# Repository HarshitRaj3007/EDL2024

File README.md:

# EDL2024
Repository for our EDL project in year 2024. RRAM Characterization using FPGA.

This repository contains the PCB design files of all the three modules (Main PCB, Resisitive crossbar array, Power PCB), HDL code, Python code used for GUI, and PCB enclosure design files.

There are 3 files for documentation:
1. Documentation for programming, laptop-FPGA interface & GUI
2. Documentation for PCB
3. Documentation for Testing(mainly Analog)

**HDL files**: EDL_merged_code encapsulates all the HDL code and the .py files for GUI. folder has a readme file that holds detailed information about the directory.

**PCB files**: MiniCircuit contains KiCAD files for a scaled-down version of the PCB intended for testing, FinalCircuit contains design files of the main PCB module, ResistiveCrossbar contains design files for a 3 $\times$ 3 resistive crossbar array and PowerConverter has the design files for the power PCB which was intended to power the entire module from wall supply of 230 V AC. 

**CAD files**: A basic PCB enclosure which can be fabricated via laser cutting can be found in the Enclosure_Fusion360.dxf file. Couldn't add the .stp file for the reference 3D design of the complete circuit due to file size restrictions in GitHub. 

**Operating Procedure**

Since the power PCB module we designed turned out to be faulty, we had to use power banks instead to supply $\pm$ 5 V, which have to connected appropriately to the corresponding pins in the main PCB module. The final design is highly user-friendly and all one needs to do after this step is to provide the parameters under which the characterization is to be executed: amplitude of the input pulse, the location of the resistor in the array, the mode of operation (RD/WR) and the requisite $R_{sense}$ location. The GUI displays both the input and output waveform for a pulse width of 100 $\mu s$, along with the estimated value of the resistance.

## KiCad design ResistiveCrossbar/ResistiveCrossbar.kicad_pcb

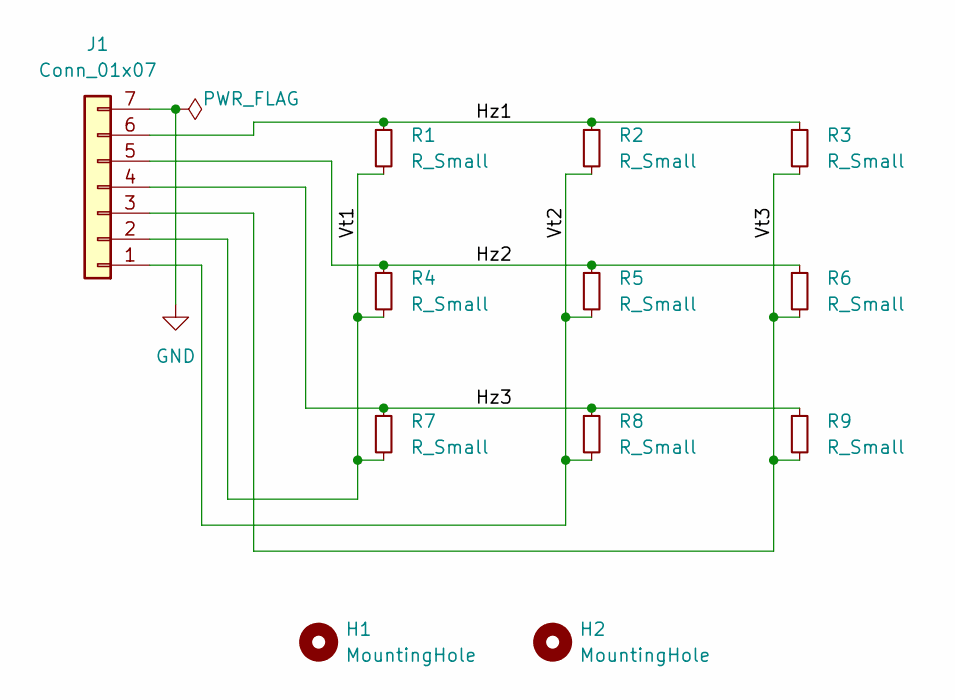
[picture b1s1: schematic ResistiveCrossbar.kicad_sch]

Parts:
H1, H2: MountingHole; MountingHole_3mm
J1: Conn_01x07; PinHeader_1x07_P2.54mm_Vertical
R1, R2, R3, R4, R5, R6, R7, R8, R9: R_Small; R_1206_3216Metric_Pad1.30x1.75mm_HandSolder

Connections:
/Hz1: J1.6, R1.1, R2.1, R3.1
/Hz2: J1.5, R4.1, R5.1, R6.1
/Hz3: J1.4, R7.1, R8.1, R9.1
/Vt1: J1.2, R1.2, R4.2, R7.2
/Vt2: J1.1, R2.2, R5.2, R8.2
/Vt3: J1.3, R3.2, R6.2, R9.2
GND: J1.7

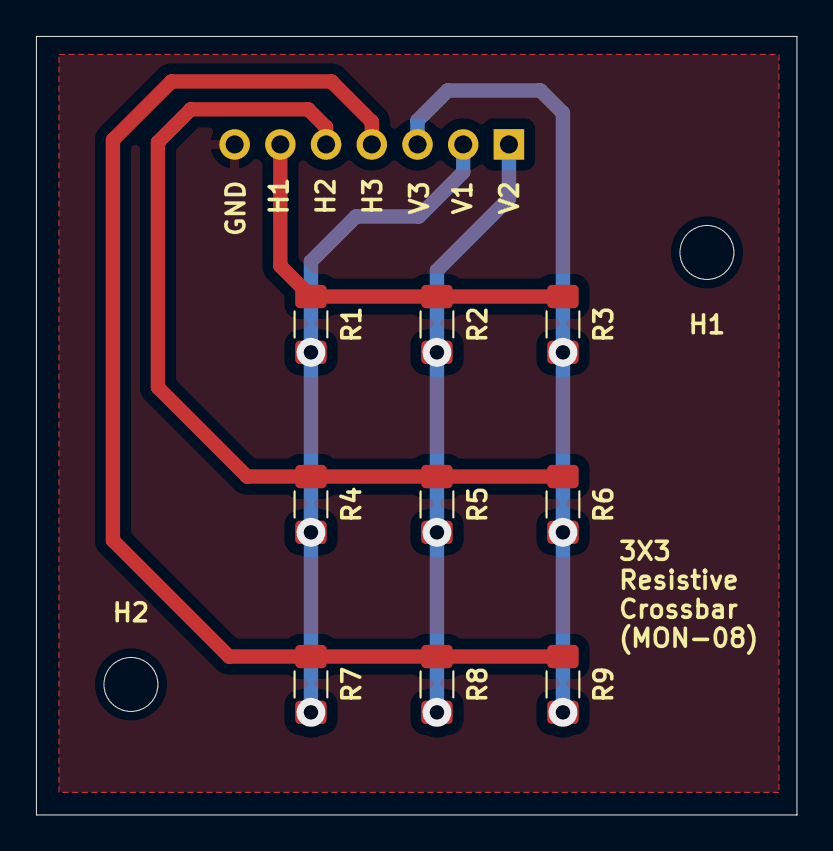
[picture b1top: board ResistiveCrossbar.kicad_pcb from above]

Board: 2 copper layers, 42.2 x 43.2 mm, 12 parts (1 on the bottom side), 6 nets.

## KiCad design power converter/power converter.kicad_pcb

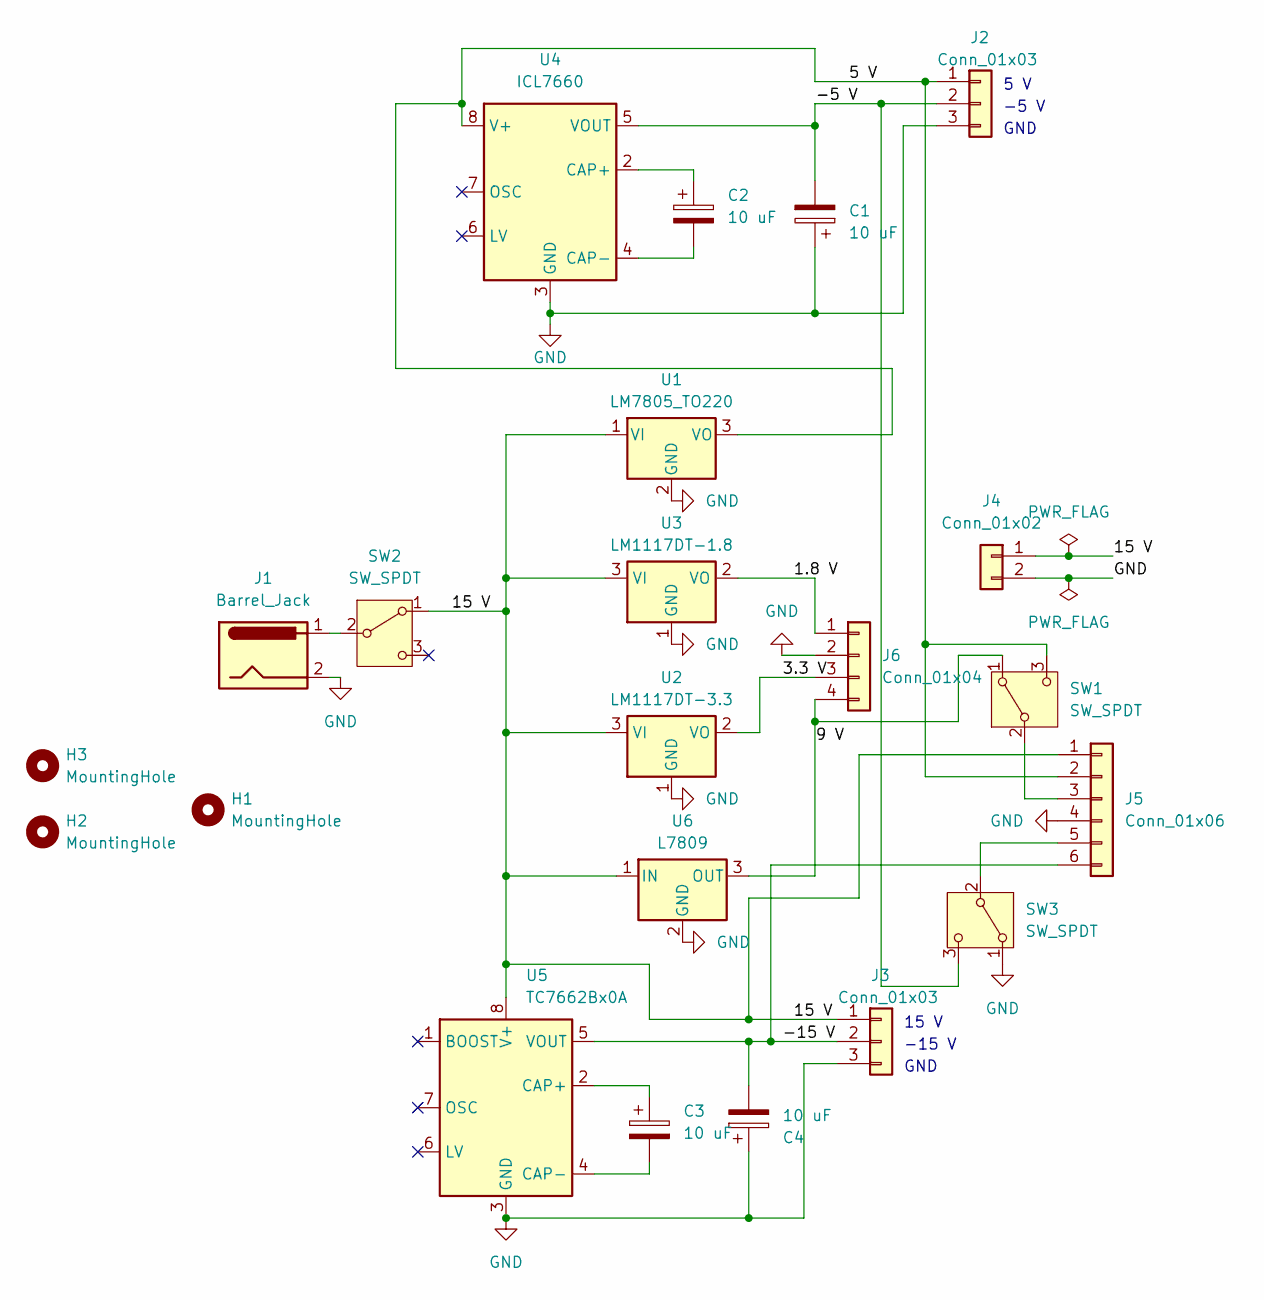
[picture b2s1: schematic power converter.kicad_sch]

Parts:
C1, C2, C3, C4: 10 uF; CP_Radial_D5.0mm_P2.50mm
H1, H2, H3: MountingHole; MountingHole_3mm
J1: Barrel_Jack; BarrelJack_Horizontal
J2, J3: Conn_01x03; PinHeader_1x03_P2.54mm_Vertical
J4: Conn_01x02; PinHeader_1x02_P2.54mm_Vertical
J5: Conn_01x06; PinSocket_1x06_P2.54mm_Vertical
J6: Conn_01x04; PinSocket_1x04_P2.54mm_Vertical
SW1, SW2, SW3: SW_SPDT; Slide_switch
U1: LM7805_TO220; TO-220-3_Vertical
U2: LM1117DT-3.3; TO-252-3_TabPin2
U3: LM1117DT-1.8; TO-252-3_TabPin2
U4: ICL7660; SOIC-8_3.9x4.9mm_P1.27mm
U5: TC7662Bx0A; SOIC-8_3.9x4.9mm_P1.27mm
U6: L7809; TO-220-3_Vertical

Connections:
/1.8 V: J6.1, U3.2 (VO)
/3.3 V: J6.3, U2.2 (VO)
/5 V: J2.1, J5.2, SW1.3 (C), U1.3 (VO), U4.8 (V+)
/9 V: J6.4, SW1.1 (A), U6.3 (OUT)
/15 V: J3.1, J4.1, J5.1, SW2.1 (A), U1.1 (VI), U2.3 (VI), U3.3 (VI), U5.8 (V+), U6.1 (IN)
/-5 V: C1.2, J2.2, SW3.3 (C), U4.5 (VOUT)
/-15 V: C4.2, J3.2, J5.6, U5.5 (VOUT)
GND: C1.1, C4.1, J1.2, J2.3, J3.3, J4.2, J5.4, J6.2, SW3.1 (A), U1.2 (GND), U2.1 (GND), U3.1 (GND), U4.3 (GND), U5.3 (GND), U6.2 (GND)
unnamed: J5.3, SW1.2 (B)
unnamed: J5.5, SW3.2 (B)
unnamed: J1.1, SW2.2 (B)
unnamed: C2.1, U4.2 (CAP+)
unnamed: C2.2, U4.4 (CAP-)
unnamed: C3.1, U5.2 (CAP+)
unnamed: C3.2, U5.4 (CAP-)

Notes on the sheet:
5 V
-15 V
GND
-5 V
15 V

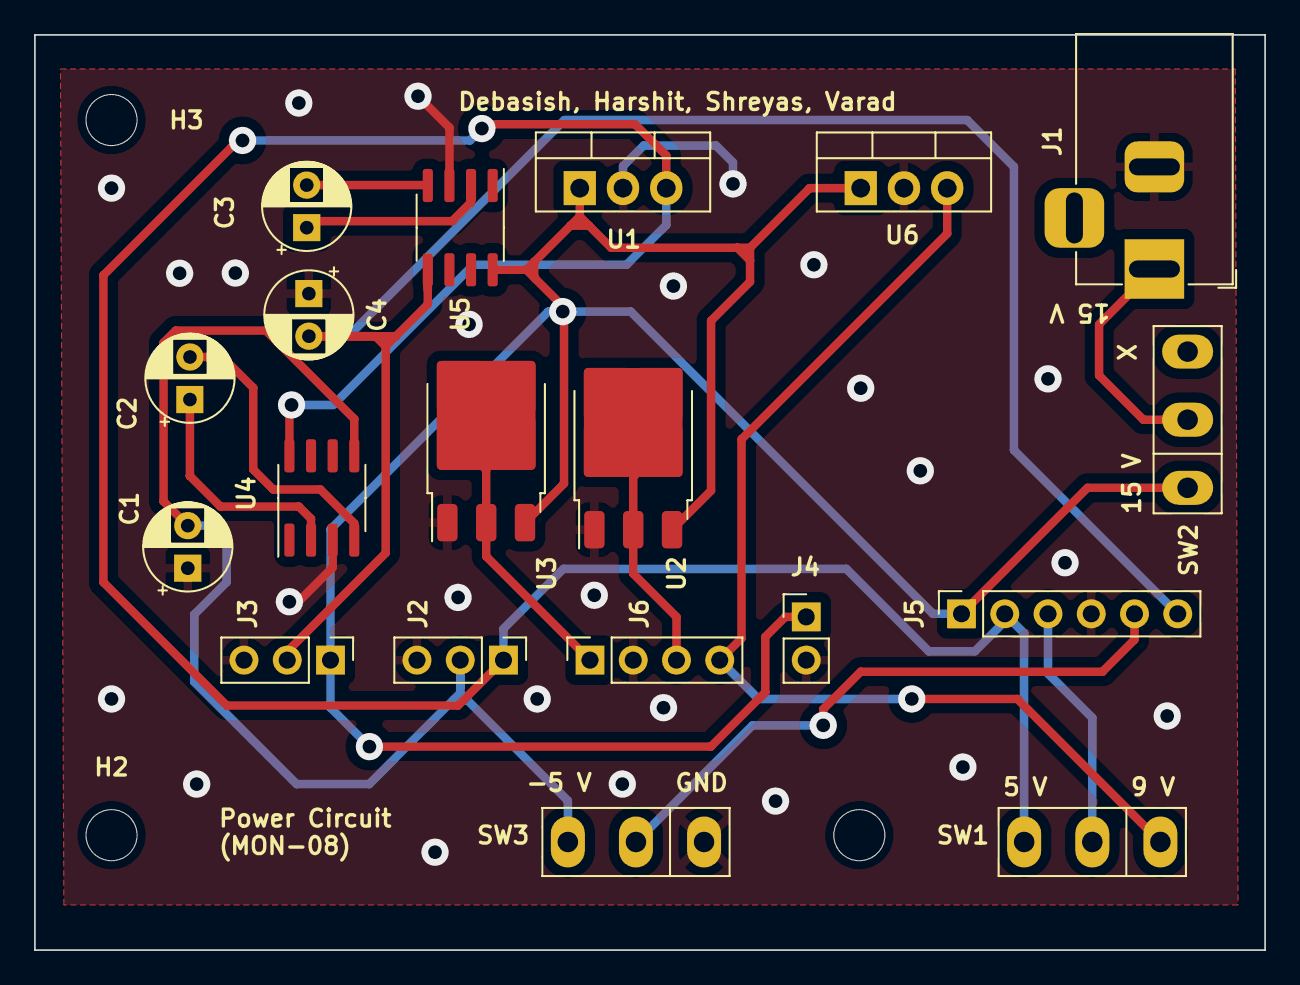
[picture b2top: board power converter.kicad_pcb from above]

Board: 2 copper layers, 72.2 x 53.8 mm, 22 parts (0 on the bottom side), 15 nets.

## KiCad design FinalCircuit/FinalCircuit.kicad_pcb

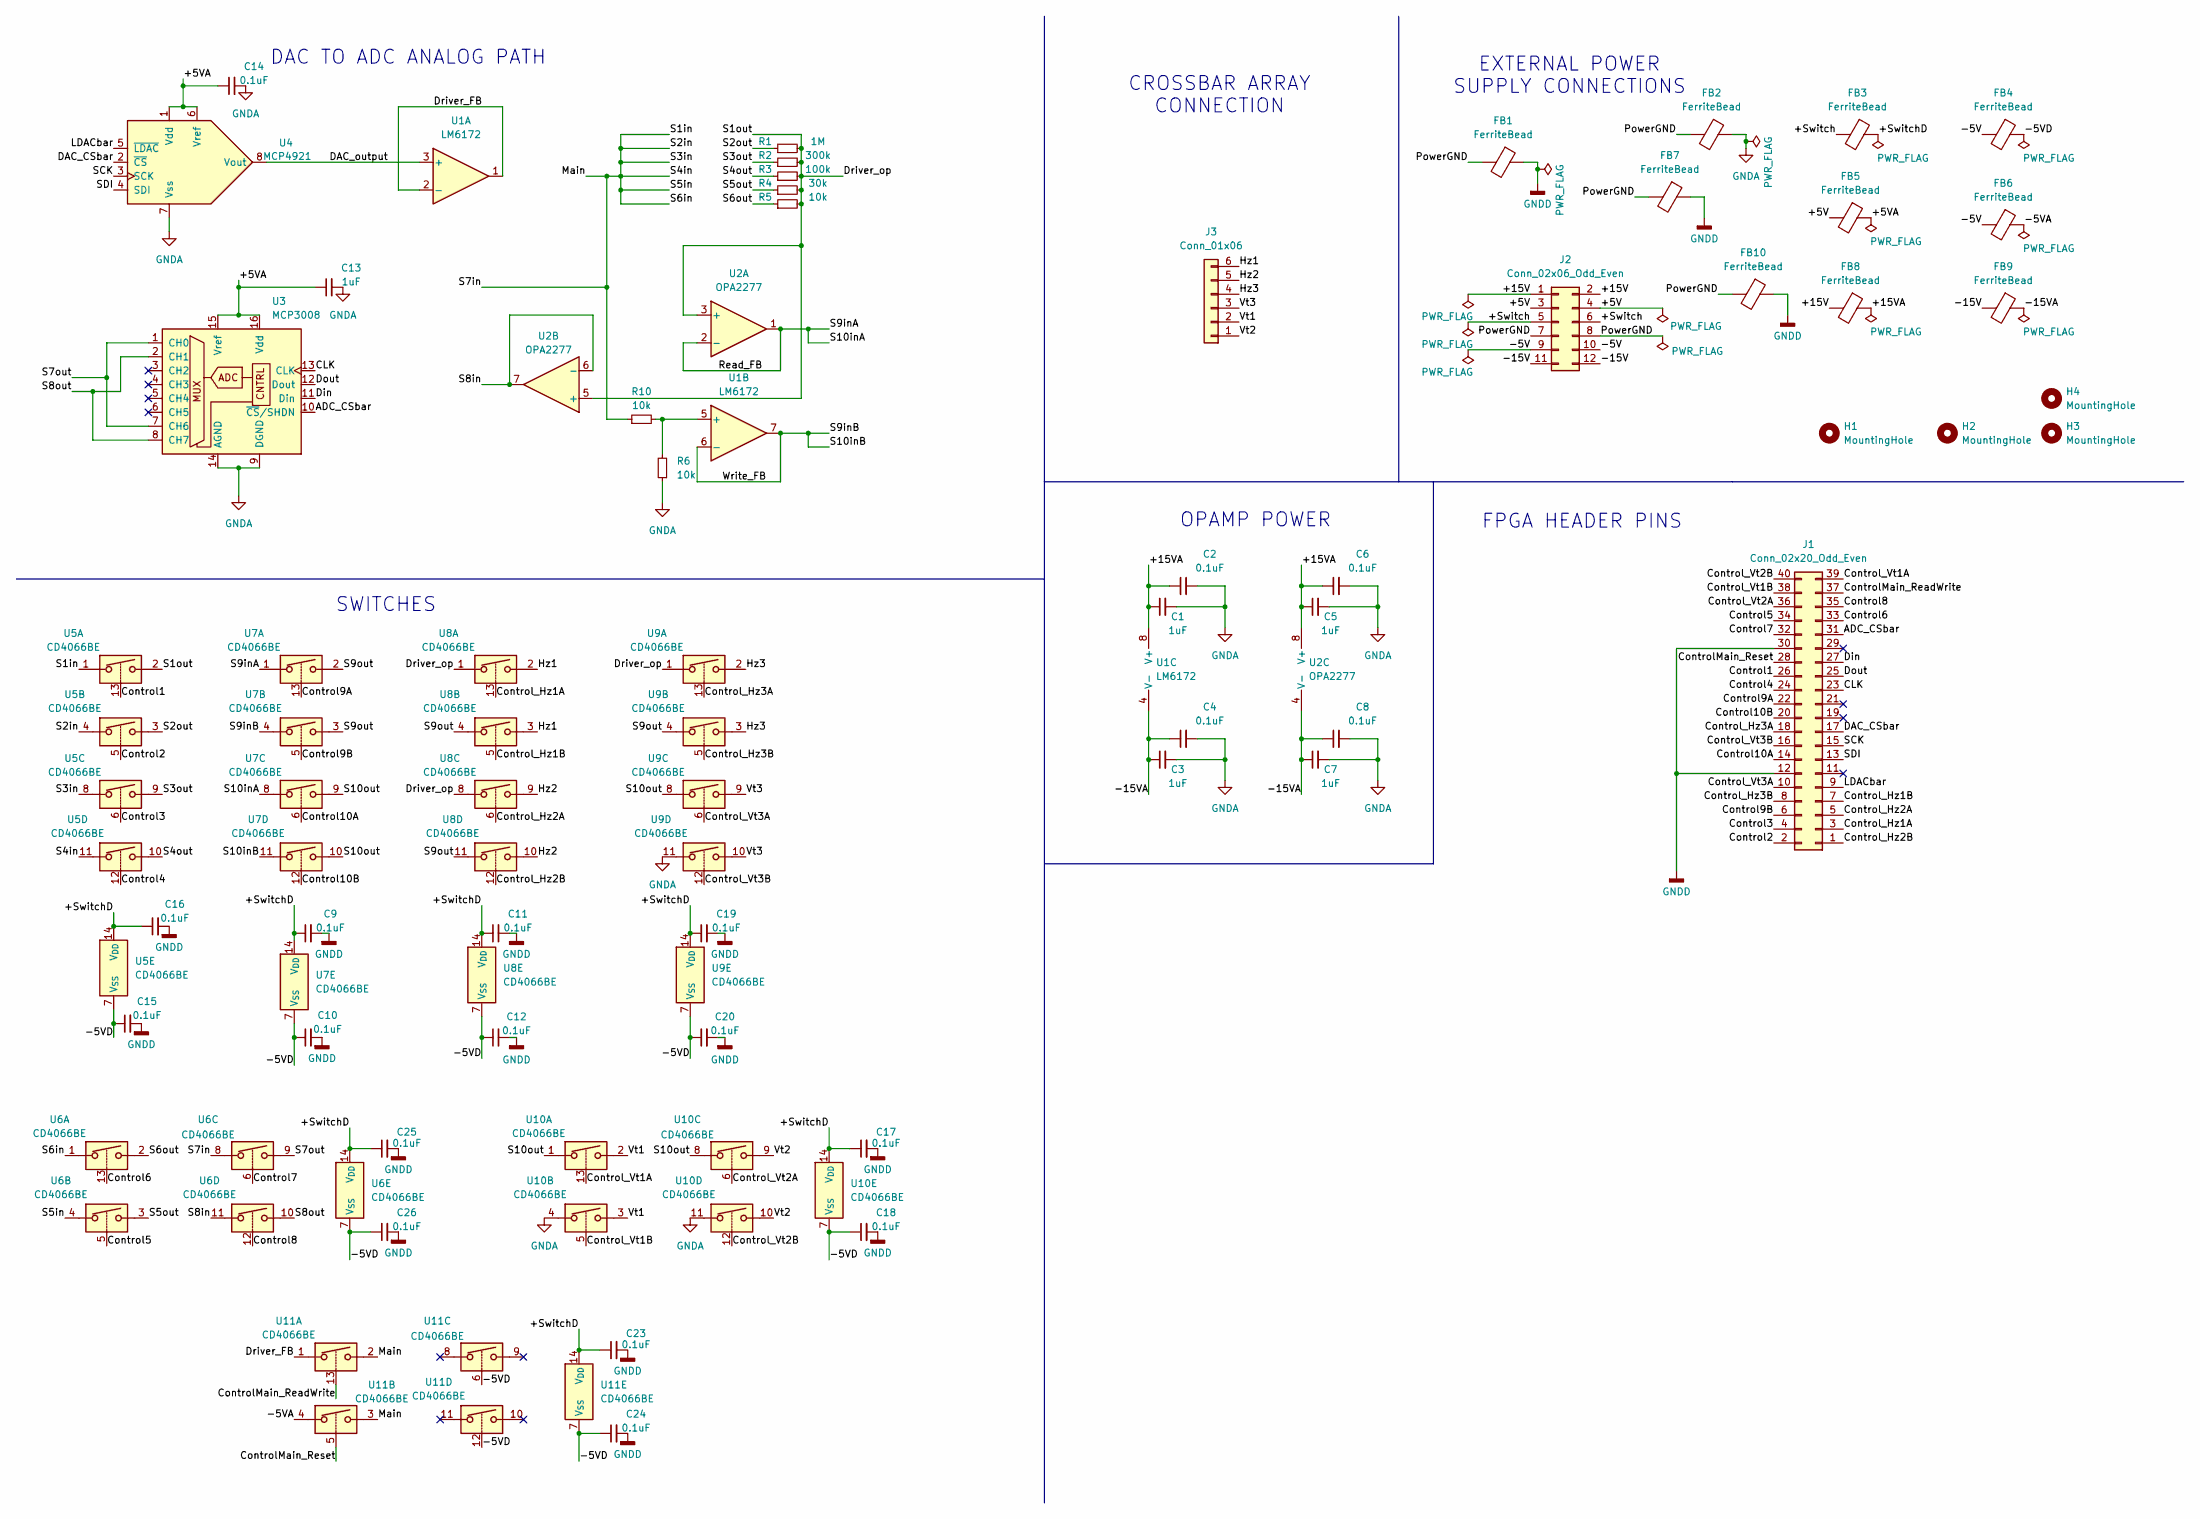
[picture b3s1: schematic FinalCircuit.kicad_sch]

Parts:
C1, C3, C5, C7, C13: 1uF; C_1206_3216Metric_Pad1.33x1.80mm_HandSolder
C2, C4, C6, C8, C9, C10, C11, C12, C14, C15, C16, C17, C18, C19, C20, C23, C24, C25, C26: 0.1uF; C_1206_3216Metric_Pad1.33x1.80mm_HandSolder
FB1, FB2, FB3, FB4, FB5, FB6, FB7, FB8, FB9, FB10: FerriteBead; L_0805_2012Metric_Pad1.15x1.40mm_HandSolder
H1, H2, H3, H4: MountingHole; MountingHole_3mm
J1: Conn_02x20_Odd_Even; PinSocket_2x20_P2.54mm_Vertical
J2: Conn_02x06_Odd_Even; PinHeader_2x06_P2.54mm_Vertical
J3: Conn_01x06; PinSocket_1x06_P2.54mm_Vertical
R1: 1M; R_1206_3216Metric_Pad1.30x1.75mm_HandSolder
R2: 300k; R_1206_3216Metric_Pad1.30x1.75mm_HandSolder
R3: 100k; R_1206_3216Metric_Pad1.30x1.75mm_HandSolder
R4: 30k; R_1206_3216Metric_Pad1.30x1.75mm_HandSolder
R5, R6, R10: 10k; R_1206_3216Metric_Pad1.30x1.75mm_HandSolder
U1: LM6172; DIP-8_W7.62mm_Socket
U2: OPA2277; DIP-8_W7.62mm_Socket
U3: MCP3008; DIP-16_W7.62mm_Socket
U4: MCP4921; DIP-8_W7.62mm_Socket
U5, U6, U7, U8, U9, U10, U11: CD4066BE; DIP-14_W7.62mm_Socket

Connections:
/+5V: FB5.2, J2.3, J2.4
/+5VA: C13.1, C14.1, FB5.1, U3.15 (Vref), U3.16 (Vdd), U4.1 (Vdd), U4.6 (Vref)
/+15V: FB8.2, J2.1, J2.2
/+15VA: C1.1, C2.1, C5.1, C6.1, FB8.1, U1.8 (V+), U2.8 (V+)
/+Switch: FB3.2, J2.5, J2.6
/+SwitchD: C9.1, C11.1, C16.1, C17.1, C19.1, C23.1, C25.1, FB3.1, U5.14 (V_{DD}), U6.14 (V_{DD}), U7.14 (V_{DD}), U8.14 (V_{DD}), U9.14 (V_{DD}), U10.14 (V_{DD}), U11.14 (V_{DD})
/-5V: FB4.2, FB6.2, J2.9, J2.10
/-5VA: FB6.1, U11.4
/-5VD: C10.1, C12.1, C15.1, C18.1, C20.1, C24.1, C26.1, FB4.1, U5.7 (V_{SS}), U6.7 (V_{SS}), U7.7 (V_{SS}), U8.7 (V_{SS}), U9.7 (V_{SS}), U10.7 (V_{SS}), U11.6, U11.7 (V_{SS}), U11.12
/-15V: FB9.2, J2.11, J2.12
/-15VA: C3.1, C4.1, C7.1, C8.1, FB9.1, U1.4 (V-), U2.4 (V-)
/ADC_CSbar: J1.31, U3.10 (~CS/SHDN)
/CLK: J1.23, U3.13 (CLK)
/Control1: J1.26, U5.13
/Control2: J1.2, U5.5
/Control3: J1.4, U5.6
/Control4: J1.24, U5.12
/Control5: J1.34, U6.5
/Control6: J1.33, U6.13
/Control7: J1.32, U6.6
/Control8: J1.35, U6.12
/Control9A: J1.22, U7.13
/Control9B: J1.6, U7.5
/Control10A: J1.14, U7.6
/Control10B: J1.20, U7.12
/ControlMain_ReadWrite: J1.37, U11.13
/ControlMain_Reset: J1.28, U11.5
/Control_Hz1A: J1.3, U8.13
/Control_Hz1B: J1.7, U8.5
/Control_Hz2A: J1.5, U8.6
/Control_Hz2B: J1.1, U8.12
/Control_Hz3A: J1.18, U9.13
/Control_Hz3B: J1.8, U9.5
/Control_Vt1A: J1.39, U10.13
/Control_Vt1B: J1.38, U10.5
/Control_Vt2A: J1.36, U10.6
/Control_Vt2B: J1.40, U10.12
/Control_Vt3A: J1.10, U9.6
/Control_Vt3B: J1.16, U9.12
/DAC_CSbar: J1.17, U4.2 (~CS)
/DAC_output: U1.3 (+), U4.8 (Vout)
/Din: J1.27, U3.11 (Din)
/Dout: J1.25, U3.12 (Dout)
/Driver_FB: U1.1, U1.2 (-), U11.1
/Driver_op: R1.2, R2.2, R3.2, R4.2, R5.2, U2.3 (+), U2.5 (+), U5.2, U8.1, U8.8, U9.1
/Hz1: J3.6, U8.2, U8.3
/Hz2: J3.5, U8.9, U8.10
/Hz3: J3.4, U9.2, U9.3
/LDACbar: J1.9, U4.5 (~LDAC)
/Main: R10.1, U5.1, U5.4, U5.8, U5.11, U6.1, U6.4, U6.8, U11.2, U11.3
/PowerGND: FB1.2, FB2.2, FB7.2, FB10.2, J2.7, J2.8
/Read_FB: U2.1, U2.2 (-), U7.1, U7.8
/S2out: R1.1, U5.3
/S3out: R2.1, U5.9
/S4out: R3.1, U5.10
/S5out: R4.1, U6.3
/S6out: R5.1, U6.2
/S7out: U3.1 (CH0), U3.7 (CH6), U6.9
/S8in: U2.6 (-), U2.7, U6.11
/S8out: U3.2 (CH1), U3.8 (CH7), U6.10
/S9out: U7.2, U7.3, U8.4, U8.11, U9.4
/S10inB: U1.6 (-), U1.7, U7.4, U7.11
/S10out: U7.9, U7.10, U9.8, U10.1, U10.8
/SCK: J1.15, U4.3 (SCK)
/SDI: J1.13, U4.4 (SDI)
/Vt1: J3.2, U10.2, U10.3
/Vt2: J3.1, U10.9, U10.10
/Vt3: J3.3, U9.9, U9.10
GNDA: C1.2, C2.2, C3.2, C4.2, C5.2, C6.2, C7.2, C8.2, C13.2, C14.2, FB2.1, R6.1, U3.9 (DGND), U3.14 (AGND), U4.7 (Vss), U9.11, U10.4, U10.11
GNDD: C9.2, C10.2, C11.2, C12.2, C15.2, C16.2, C17.2, C18.2, C19.2, C20.2, C23.2, C24.2, C25.2, C26.2, FB1.1, FB7.1, FB10.1, J1.12, J1.30
unnamed: R6.2, R10.2, U1.5 (+)

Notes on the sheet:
SWITCHES
CROSSBAR ARRAY CONNECTION
DAC TO ADC ANALOG PATH
OPAMP POWER
EXTERNAL POWER SUPPLY CONNECTIONS
FPGA HEADER PINS

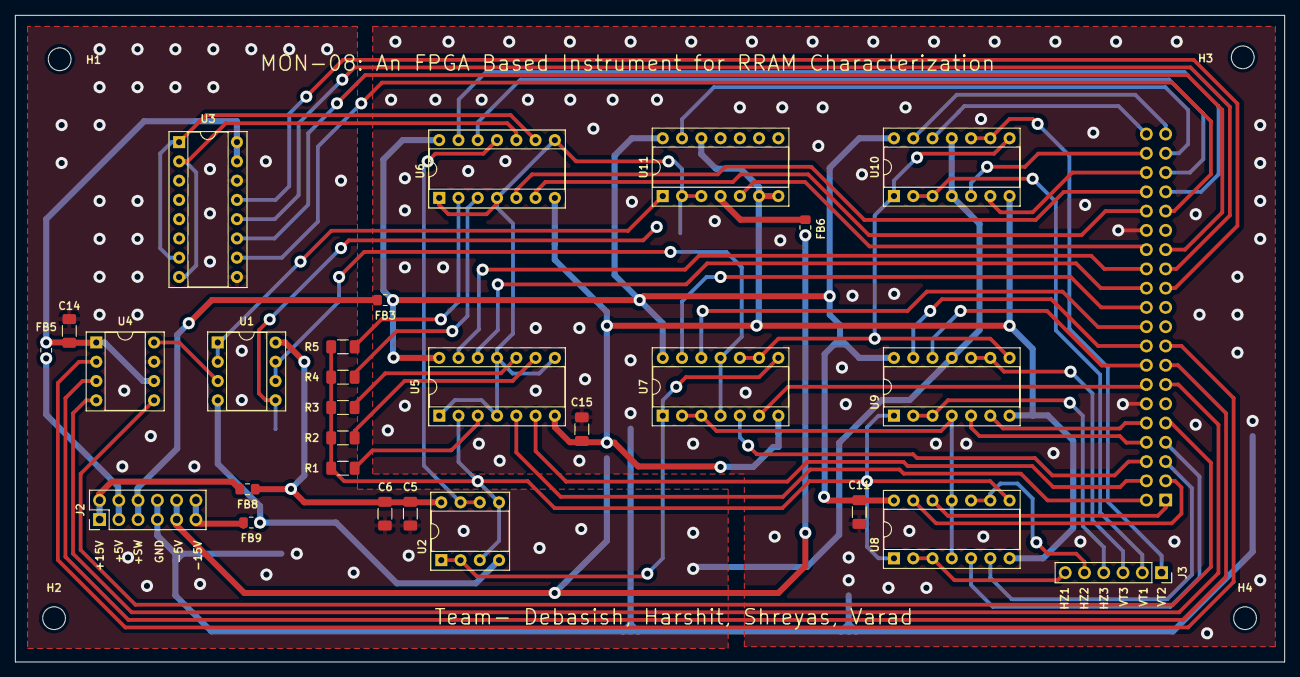
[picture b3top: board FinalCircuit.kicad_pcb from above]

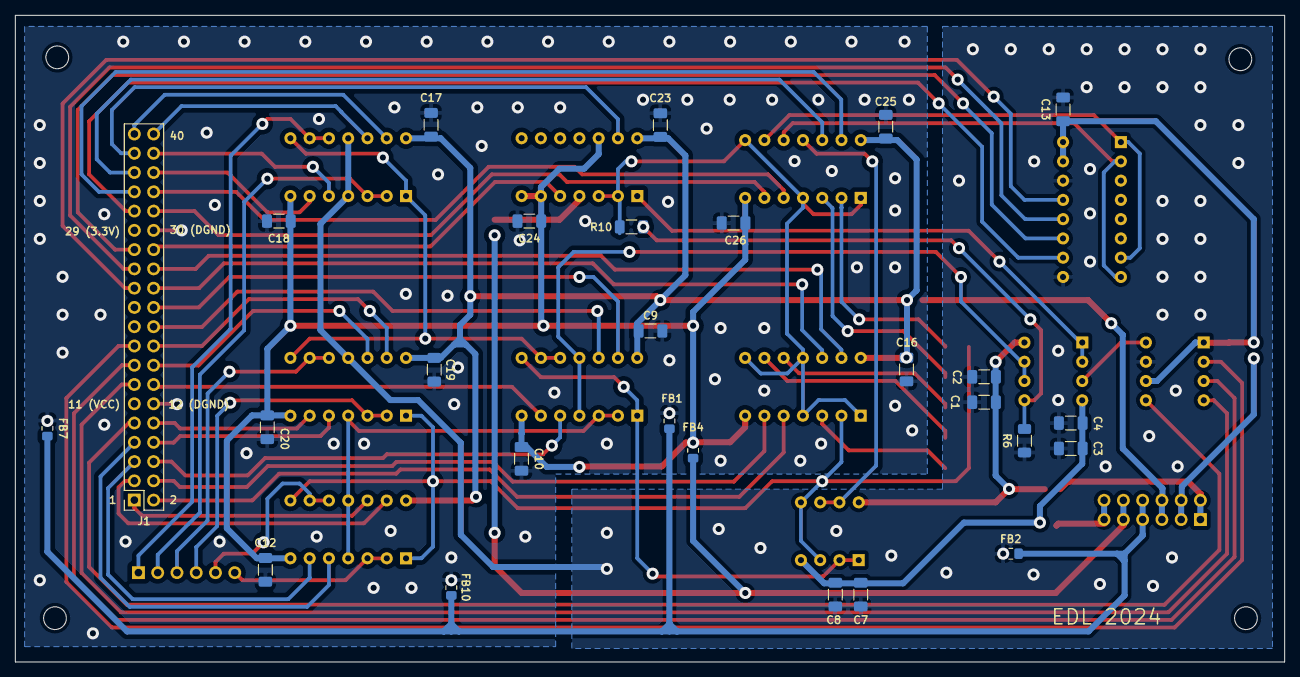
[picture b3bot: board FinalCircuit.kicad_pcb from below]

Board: 2 copper layers, 167.3 x 85.2 mm, 59 parts (27 on the bottom side), 71 nets.

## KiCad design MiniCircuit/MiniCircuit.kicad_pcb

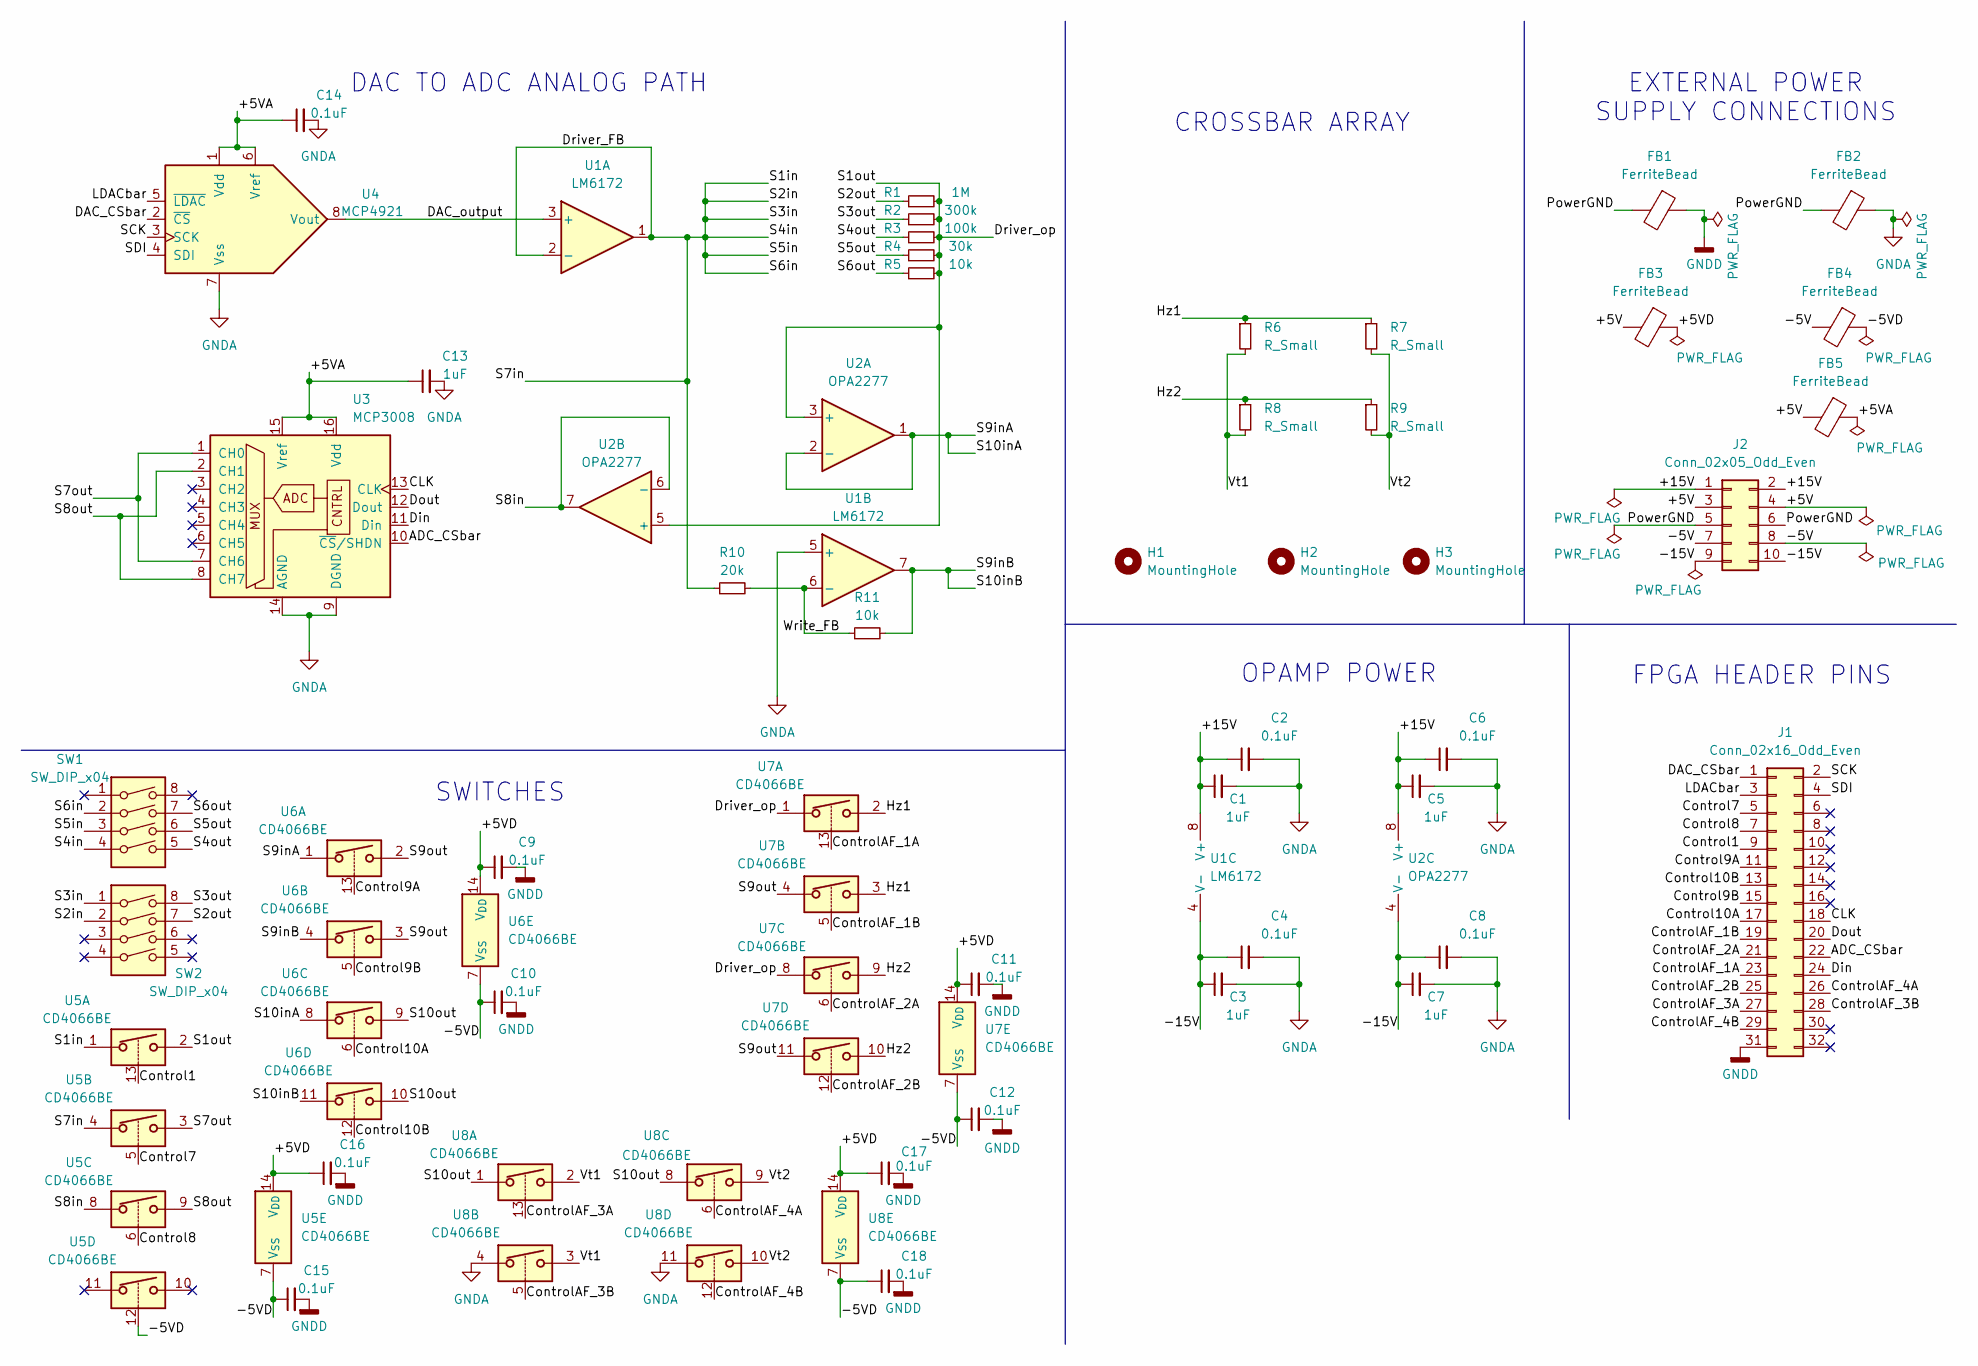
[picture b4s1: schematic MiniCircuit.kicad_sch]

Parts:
C1, C3, C5, C7, C13: 1uF; C_1206_3216Metric_Pad1.33x1.80mm_HandSolder
C2, C4, C6, C8, C9, C10, C11, C12, C14, C15, C16, C17, C18: 0.1uF; C_1206_3216Metric_Pad1.33x1.80mm_HandSolder
FB1, FB2, FB3, FB4, FB5: FerriteBead; L_0805_2012Metric_Pad1.15x1.40mm_HandSolder
H1, H2, H3: MountingHole; MountingHole_3mm
J1: Conn_02x16_Odd_Even; PinSocket_2x16_P2.54mm_Vertical
J2: Conn_02x05_Odd_Even; PinHeader_2x05_P2.54mm_Vertical
R1: 1M; R_1206_3216Metric_Pad1.30x1.75mm_HandSolder
R2: 300k; R_1206_3216Metric_Pad1.30x1.75mm_HandSolder
R3: 100k; R_1206_3216Metric_Pad1.30x1.75mm_HandSolder
R4: 30k; R_1206_3216Metric_Pad1.30x1.75mm_HandSolder
R5, R11: 10k; R_1206_3216Metric_Pad1.30x1.75mm_HandSolder
R6, R7, R8, R9: R_Small; R_1206_3216Metric_Pad1.30x1.75mm_HandSolder
R10: 20k; R_1206_3216Metric_Pad1.30x1.75mm_HandSolder
SW1, SW2: SW_DIP_x04; SW_DIP_SPSTx04_Slide_9.78x12.34mm_W7.62mm_P2.54mm
U1: LM6172; DIP-8_W7.62mm_Socket
U2: OPA2277; DIP-8_W7.62mm_Socket
U3: MCP3008; DIP-16_W7.62mm_Socket
U4: MCP4921; DIP-8_W7.62mm_Socket
U5, U6, U7, U8: CD4066BE; DIP-14_W7.62mm_Socket

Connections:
/+5V: FB3.2, FB5.2, J2.3, J2.4
/+5VA: C13.1, C14.1, FB5.1, U3.15 (Vref), U3.16 (Vdd), U4.1 (Vdd), U4.6 (Vref)
/+5VD: C9.1, C11.1, C16.1, C17.1, FB3.1, U5.14 (V_{DD}), U6.14 (V_{DD}), U7.14 (V_{DD}), U8.14 (V_{DD})
/+15V: C1.1, C2.1, C5.1, C6.1, J2.1, J2.2, U1.8 (V+), U2.8 (V+)
/-5V: FB4.2, J2.7, J2.8
/-5VD: C10.1, C12.1, C15.1, C18.1, FB4.1, U5.7 (V_{SS}), U5.12, U6.7 (V_{SS}), U7.7 (V_{SS}), U8.7 (V_{SS})
/-15V: C3.1, C4.1, C7.1, C8.1, J2.9, J2.10, U1.4 (V-), U2.4 (V-)
/ADC_CSbar: J1.22, U3.10 (~CS/SHDN)
/CLK: J1.18, U3.13 (CLK)
/Control1: J1.9, U5.13
/Control7: J1.5, U5.5
/Control8: J1.7, U5.6
/Control9A: J1.11, U6.13
/Control9B: J1.15, U6.5
/Control10A: J1.17, U6.6
/Control10B: J1.13, U6.12
/ControlAF_1A: J1.23, U7.13
/ControlAF_1B: J1.19, U7.5
/ControlAF_2A: J1.21, U7.6
/ControlAF_2B: J1.25, U7.12
/ControlAF_3A: J1.27, U8.13
/ControlAF_3B: J1.28, U8.5
/ControlAF_4A: J1.26, U8.6
/ControlAF_4B: J1.29, U8.12
/DAC_CSbar: J1.1, U4.2 (~CS)
/DAC_output: U1.3 (+), U4.8 (Vout)
/Din: J1.24, U3.11 (Din)
/Dout: J1.20, U3.12 (Dout)
/Driver_FB: R10.1, SW1.2, SW1.3, SW1.4, SW2.1, SW2.2, U1.1, U1.2 (-), U5.1, U5.4
/Driver_op: R1.2, R2.2, R3.2, R4.2, R5.2, U2.3 (+), U2.5 (+), U5.2, U7.1, U7.8
/Hz1: R6.1, R7.1, U7.2, U7.3
/Hz2: R8.1, R9.1, U7.9, U7.10
/LDACbar: J1.3, U4.5 (~LDAC)
/PowerGND: FB1.2, FB2.2, J2.5, J2.6
/S2out: R1.1, SW2.7
/S3out: R2.1, SW2.8
/S4out: R3.1, SW1.5
/S5out: R4.1, SW1.6
/S6out: R5.1, SW1.7
/S7out: U3.1 (CH0), U3.7 (CH6), U5.3
/S8in: U2.6 (-), U2.7, U5.8
/S8out: U3.2 (CH1), U3.8 (CH7), U5.9
/S9out: U6.2, U6.3, U7.4, U7.11
/S10inA: U2.1, U2.2 (-), U6.1, U6.8
/S10inB: R11.2, U1.7, U6.4, U6.11
/S10out: U6.9, U6.10, U8.1, U8.8
/SCK: J1.2, U4.3 (SCK)
/SDI: J1.4, U4.4 (SDI)
/Vt1: R6.2, R8.2, U8.2, U8.3
/Vt2: R7.2, R9.2, U8.9, U8.10
/Write_FB: R10.2, R11.1, U1.6 (-)
GNDA: C1.2, C2.2, C3.2, C4.2, C5.2, C6.2, C7.2, C8.2, C13.2, C14.2, FB2.1, U1.5 (+), U3.9 (DGND), U3.14 (AGND), U4.7 (Vss), U8.4, U8.11
GNDD: C9.2, C10.2, C11.2, C12.2, C15.2, C16.2, C17.2, C18.2, FB1.1, J1.31

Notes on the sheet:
SWITCHES
CROSSBAR ARRAY
DAC TO ADC ANALOG PATH
OPAMP POWER
EXTERNAL POWER SUPPLY CONNECTIONS
FPGA HEADER PINS

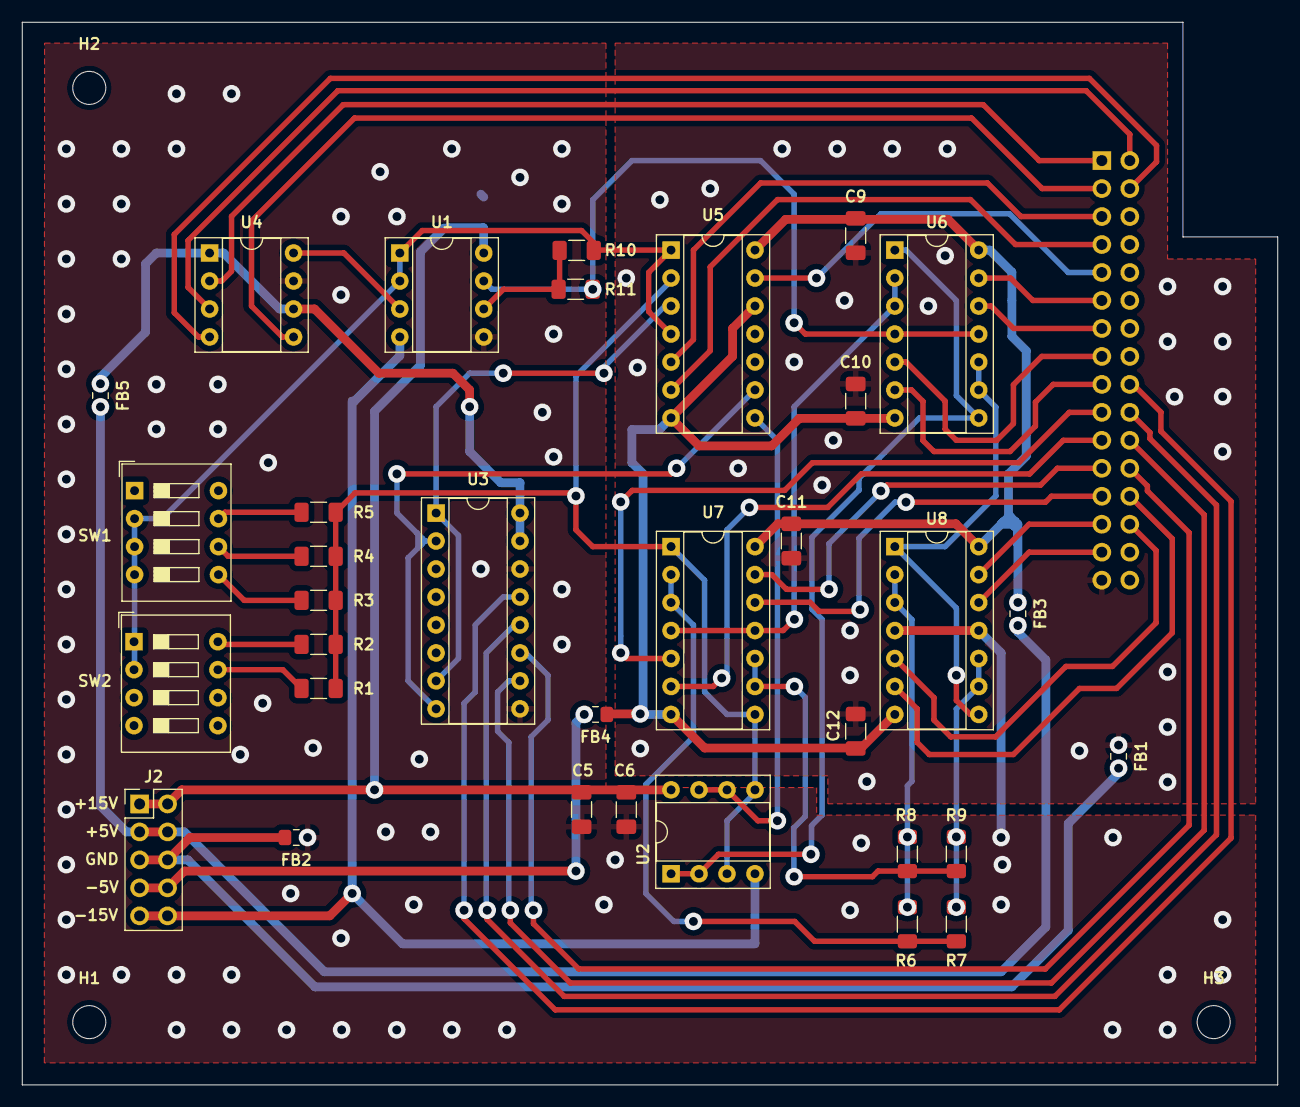
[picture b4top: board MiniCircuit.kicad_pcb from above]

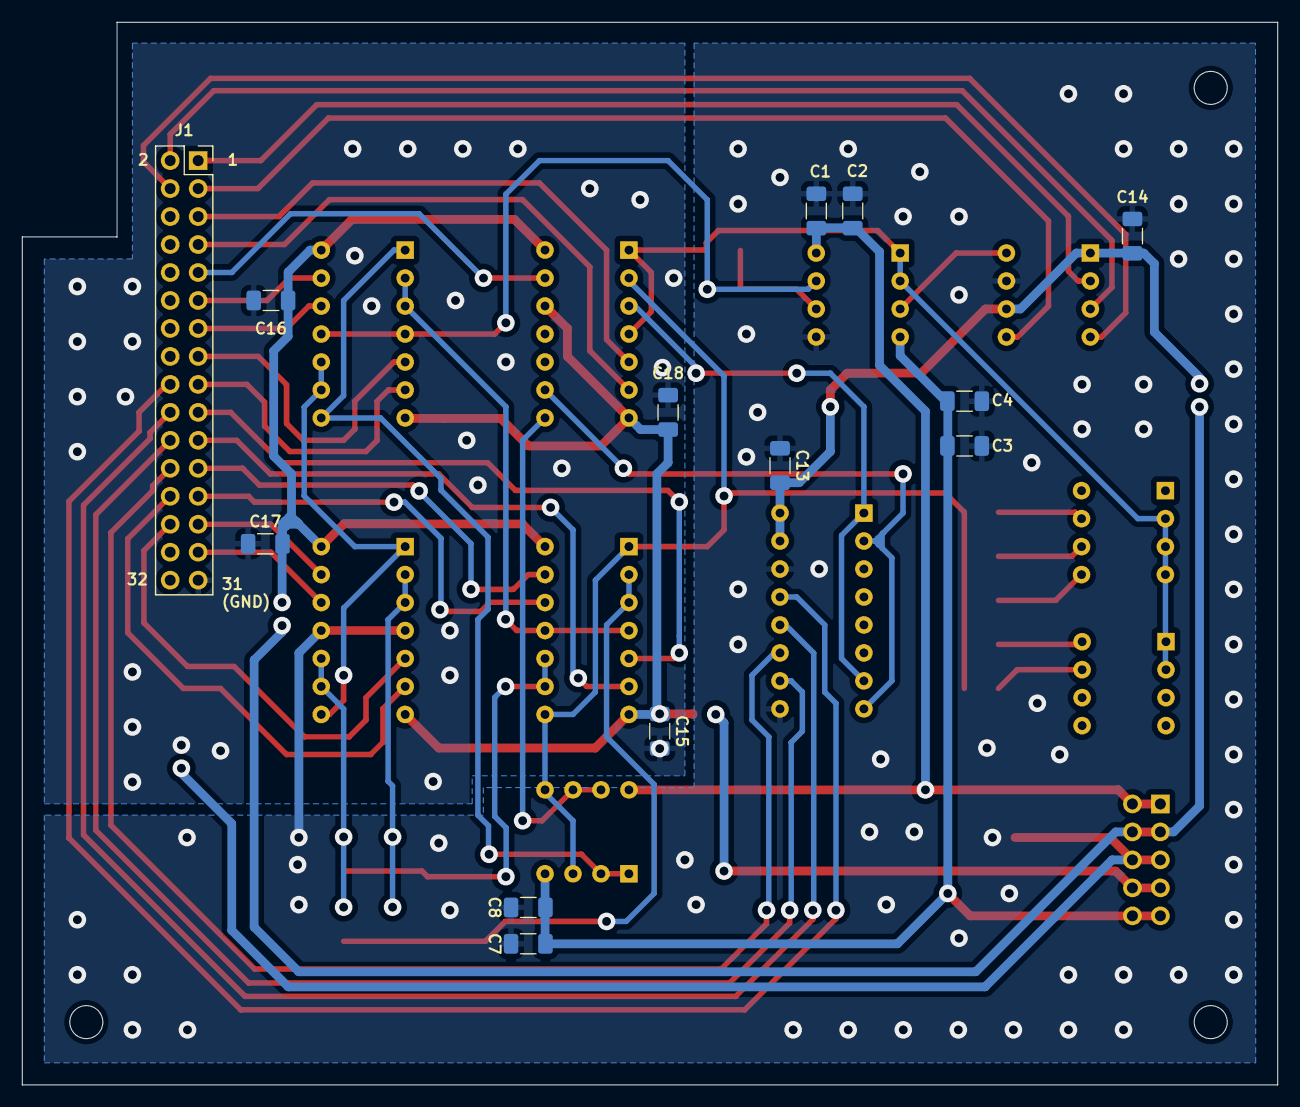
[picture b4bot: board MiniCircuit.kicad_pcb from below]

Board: 2 copper layers, 114.0 x 96.5 mm, 49 parts (13 on the bottom side), 53 nets.

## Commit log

2024-03-18 Testing Circuit Schematic and half designed PCB added. Extra Component footprints also added but only MAX4737 is reliable (Mouser)
2024-03-18 modified path of footprint library
2024-03-19 Everything done except routing of digital signals and adding Vias
2024-03-21 Initial Commit with MAX4737 Switches. Branch will now be used to change switches to CD4066
2024-03-21 Changed Schematic to include CD4066 instead of MAX4737. Design Constraints, Routing and Layout remaining
2024-03-21 PCB Done, only final touch and verification necessary
2024-03-21 All errors and warnings rectified. Silkscreen contents added.
2024-03-21 PCB Complete. Self verification left.
2024-03-22 Verified PCB, near final testing
2024-03-22 Modified as per final component footprints
2024-03-22 Added final touches
2024-03-22 Changed some reference text thickness to match Design Constraints (altho, won't be printed)
2024-03-22 Revised PCB as told by PCB Lab
2024-03-29 Add meeting notes link
2024-03-29 presentations and schematic
2024-03-31 Add milestone-3 presentation
2024-03-31 Created FinalPCB Project. All routing except control lines done.
2024-03-31 Almost all connections done. Digital traces seem too long at the moment.
2024-04-01 all FPGA files before combining
2024-04-01 Final PCB all routing done, 0 errors. Verification left
2024-04-01 Found an error in LM6172 connection. Routing of that is left.
2024-04-01 Final PCB Done. Resistive Crossbar PCB Done. Verification left.
2024-04-02 Stage 2 verification done. Holes and connectors aligned. Final verification at PCB Lab left.
2024-04-02 Some more alignments completed. Verification done again. Final order left.
2024-04-02 Some minor silkscreen changes and constraints.
2024-04-03 PCB Layout and routing of all PCBs added as per the final accepted version by the PCB Lab.
2024-04-09 comm + DAC + ADC all working
2024-04-09 fully functional FSM with comms + ADC + DAC
2024-04-10 building up the array transfer
2024-04-10 fully functional oscilloscope with buffer implemented
2024-04-11 control signals tried on PCB
2024-04-11 fixed control lines to PCB with crossbar PCB and elementary ADC
2024-04-13 fully working oscilloscope with correct communication to laptop through jtag uart
2024-04-14 sampling of ADC and transmission to PC correct, no controls
2024-04-14 FSM fully ready, need to map control signals and pulse width, get both channels to sample, let switches be se first and then have the DAC send o/p
2024-04-17 final gui working
2024-04-19 added milestone-4 slidees
2024-04-19 PCB Enclosure
    Size of .stp file was too large to be added to GitHub
2024-04-19 Final FPGA code commit, with end-to-end functionality inclusive of GUI
2024-04-19 removed meeting notes
2024-04-19 Added experiments upto milestone 3
2024-04-19 Create README.md for HDL + GUI
2024-04-19 Added Documentation
2024-04-19 Rename PCB.pdf to EDL PCB Documentation.pdf
2024-04-19 Delete Components Library directory
    This folder was used in the ideal circuit schematic and ideal circuit pcb which is not used here, hence deleting
